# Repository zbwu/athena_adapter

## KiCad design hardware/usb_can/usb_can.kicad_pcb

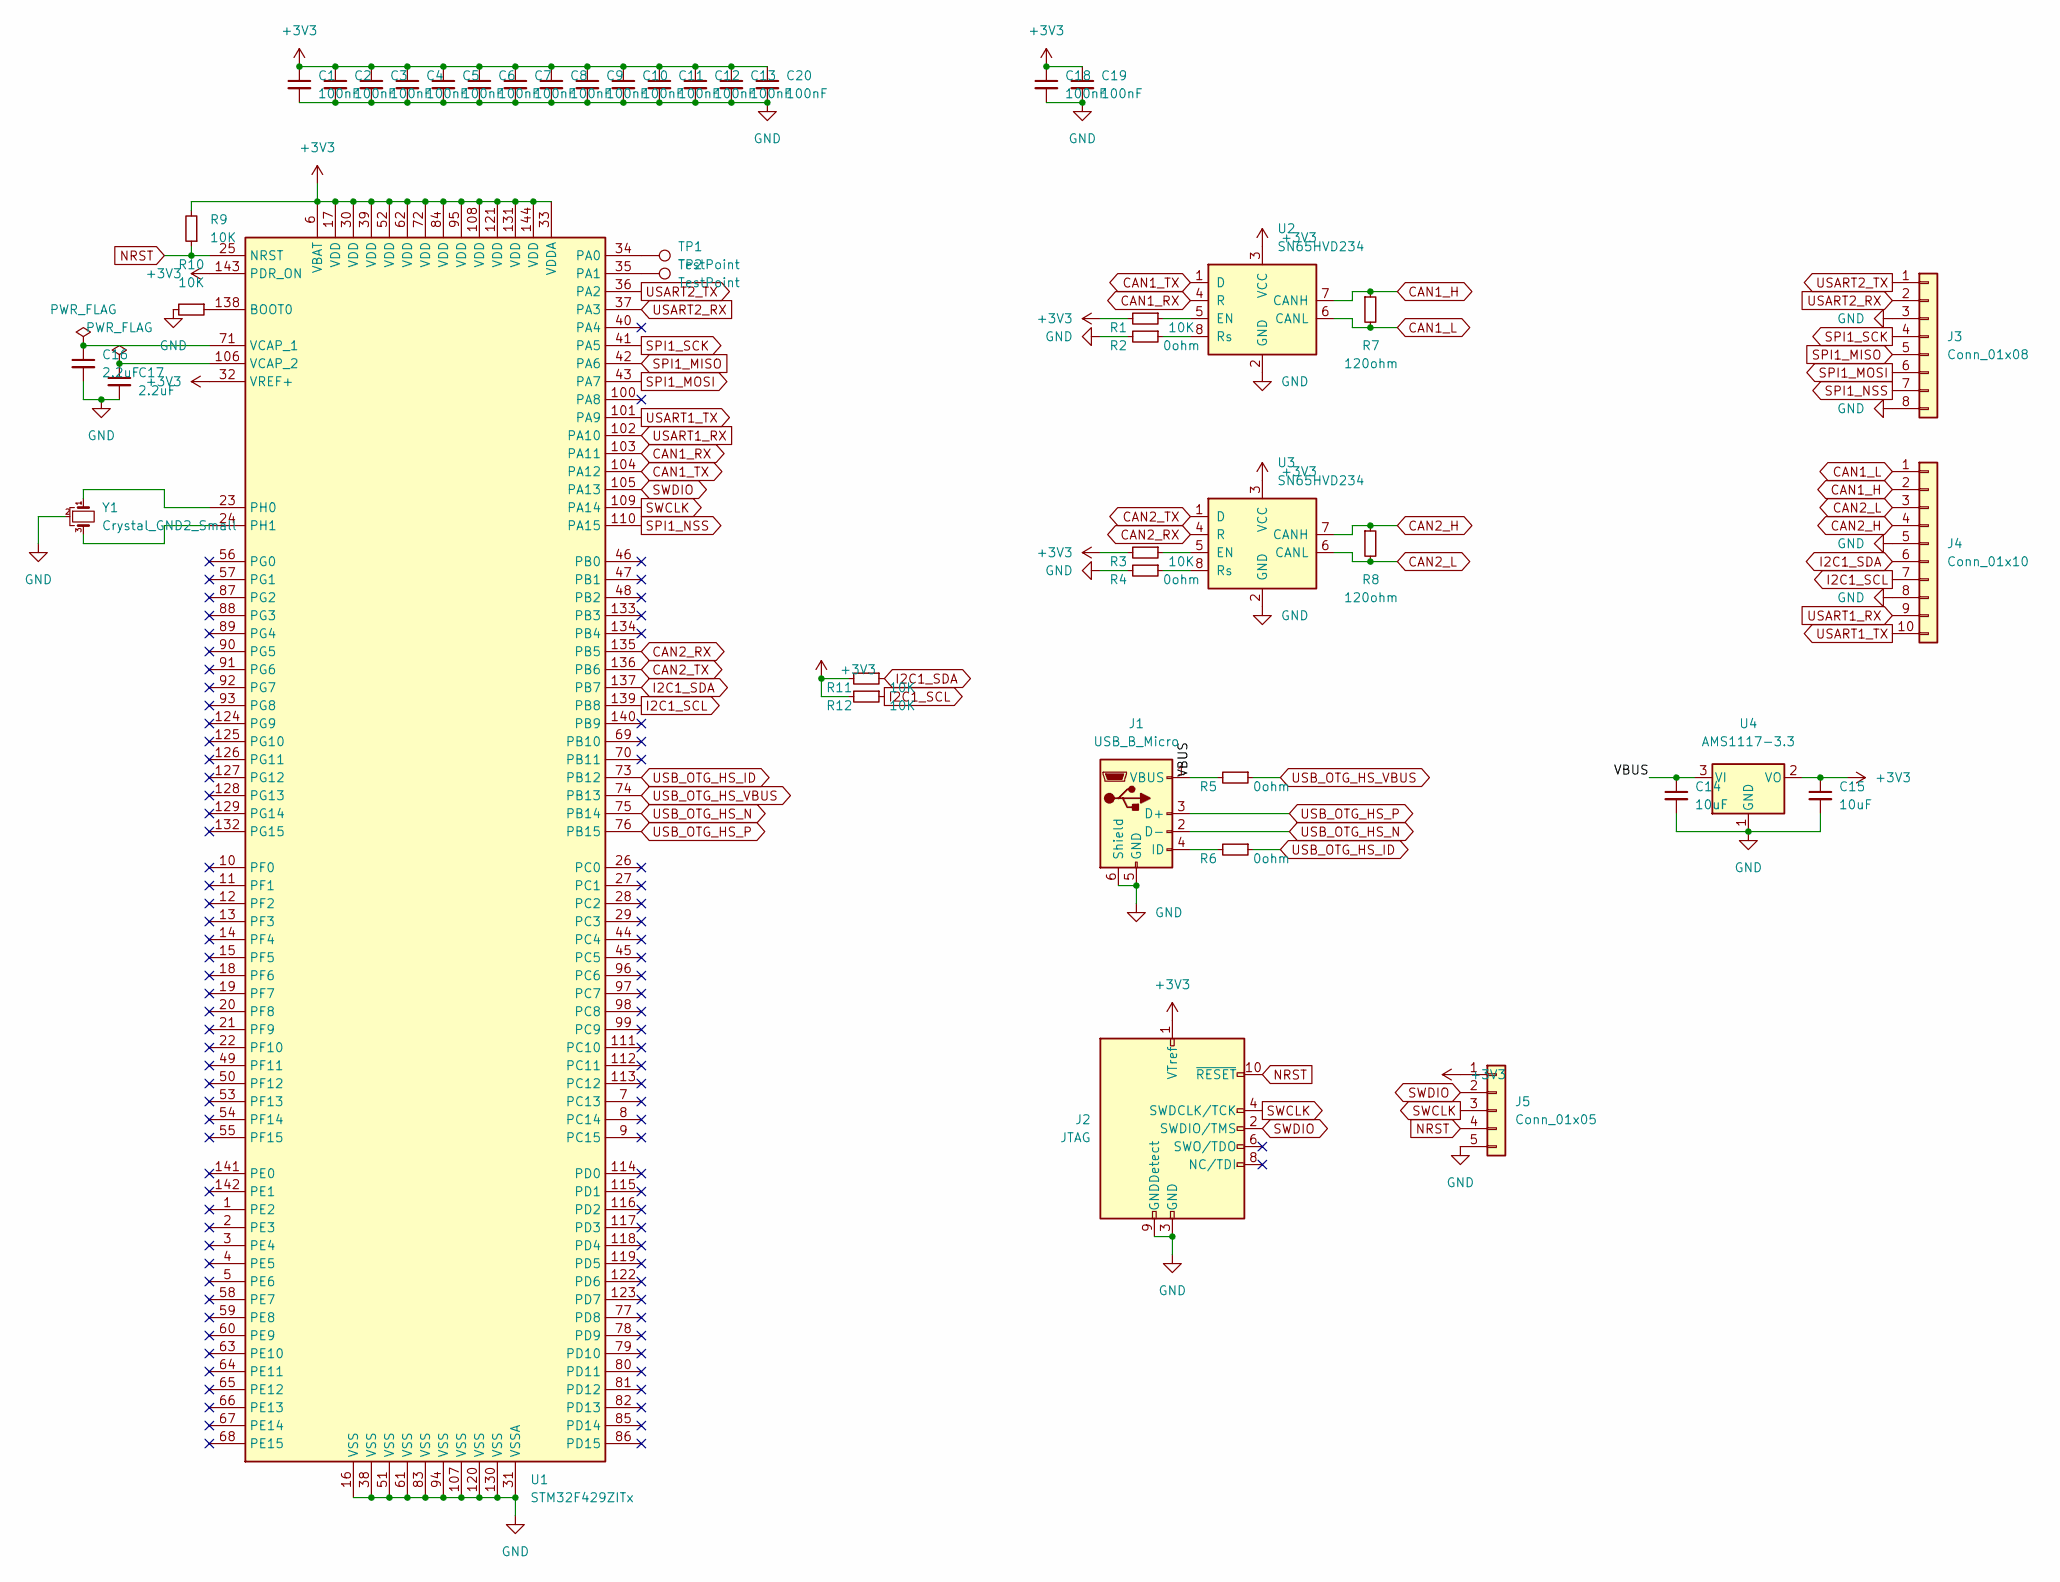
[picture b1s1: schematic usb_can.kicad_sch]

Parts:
C1, C2, C3, C4, C5, C6, C7, C8, C9, C10, C11, C12, C13, C18, C19, C20: 100nF; C_0603_1608Metric_Pad1.08x0.95mm_HandSolder
C14, C15: 10uF; C_1206_3216Metric_Pad1.33x1.80mm_HandSolder
C16, C17: 2.2uF; C_1206_3216Metric_Pad1.33x1.80mm_HandSolder
J1: USB_B_Micro; USB_Micro-B_YourCee_7.2_16Pin
J2: JTAG; PinHeader_2x05_P1.27mm_Vertical_SMD
J3: Conn_01x08; Harwin_M20-89008xx_1x08_P2.54mm_Horizontal
J4: Conn_01x10; Harwin_M20-89010xx_1x10_P2.54mm_Horizontal
J5: Conn_01x05; Harwin_M20-89005xx_1x05_P2.54mm_Horizontal
R1, R3, R9, R10, R11, R12: 10K; R_0603_1608Metric_Pad0.98x0.95mm_HandSolder
R2, R4, R5, R6: 0ohm; R_0603_1608Metric_Pad0.98x0.95mm_HandSolder
R7, R8: 120ohm; R_0603_1608Metric_Pad0.98x0.95mm_HandSolder
TP1, TP2: TestPoint; TestPoint_Pad_D1.5mm
U1: STM32F429ZITx; LQFP-144_20x20mm_P0.5mm
U2, U3: SN65HVD234; SOIC-8_3.9x4.9mm_P1.27mm
U4: AMS1117-3.3; SOT-223-3_TabPin2
Y1: Crystal_GND2_Small; CSTNE8M00GH5L000R0

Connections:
+3V3: C1.1, C2.1, C3.1, C4.1, C5.1, C6.1, C7.1, C8.1, C9.1, C10.1, C11.1, C12.1, C13.1, C15.1, C18.1, C19.1, C20.1, J2.1 (VTref), J5.1, R1.2, R3.2, R9.2, R11.2, R12.2, U1.6 (VBAT), U1.17 (VDD), U1.30 (VDD), U1.32 (VREF+), U1.33 (VDDA), U1.39 (VDD), U1.52 (VDD), U1.62 (VDD), U1.72 (VDD), U1.84 (VDD), U1.95 (VDD), U1.108 (VDD), U1.121 (VDD), U1.131 (VDD), U1.143 (PDR_ON), U1.144 (VDD), U2.3 (VCC), U3.3 (VCC), U4.2 (VO)
/VBUS: C14.1, J1.1 (VBUS), R5.2, U4.3 (VI)
CAN1_H: J4.2, R7.1, U2.7 (CANH)
CAN1_L: J4.1, R7.2, U2.6 (CANL)
CAN1_RX: U1.103 (PA11), U2.4 (R)
CAN1_TX: U1.104 (PA12), U2.1 (D)
CAN2_H: J4.4, R8.1, U3.7 (CANH)
CAN2_L: J4.3, R8.2, U3.6 (CANL)
CAN2_RX: U1.135 (PB5), U3.4 (R)
CAN2_TX: U1.136 (PB6), U3.1 (D)
GND: C1.2, C2.2, C3.2, C4.2, C5.2, C6.2, C7.2, C8.2, C9.2, C10.2, C11.2, C12.2, C13.2, C14.2, C15.2, C16.2, C17.2, C18.2, C19.2, C20.2, J1.5 (GND), J1.6 (Shield), J2.3 (GND), J2.5 (GND), J2.9 (GNDDetect), J3.3, J3.8, J4.5, J4.8, J5.5, R2.2, R4.2, R10.2, U1.16 (VSS), U1.31 (VSSA), U1.38 (VSS), U1.51 (VSS), U1.61 (VSS), U1.83 (VSS), U1.94 (VSS), U1.107 (VSS), U1.120 (VSS), U1.130 (VSS), U2.2 (GND), U3.2 (GND), U4.1 (GND), Y1.2
I2C1_SCL: J4.7, R12.1, U1.139 (PB8)
I2C1_SDA: J4.6, R11.1, U1.137 (PB7)
NRST: J2.10 (~RESET), J5.4, R9.1, U1.25 (NRST)
unnamed: C16.1, U1.71 (VCAP_1)
unnamed: C17.1, U1.106 (VCAP_2)
unnamed: J1.4 (ID), R6.2
unnamed: R1.1, U2.5 (EN)
unnamed: R2.1, U2.8 (Rs)
unnamed: R3.1, U3.5 (EN)
unnamed: R4.1, U3.8 (Rs)
unnamed: R10.1, U1.138 (BOOT0)
unnamed: TP1.1, U1.34 (PA0)
unnamed: TP2.1, U1.35 (PA1)
unnamed: U1.23 (PH0), Y1.1
unnamed: U1.24 (PH1), Y1.3
SPI1_MISO: J3.5, U1.42 (PA6)
SPI1_MOSI: J3.6, U1.43 (PA7)
SPI1_NSS: J3.7, U1.110 (PA15)
SPI1_SCK: J3.4, U1.41 (PA5)
SWCLK: J2.4 (SWDCLK/TCK), J5.3, U1.109 (PA14)
SWDIO: J2.2 (SWDIO/TMS), J5.2, U1.105 (PA13)
USART1_RX: J4.9, U1.102 (PA10)
USART1_TX: J4.10, U1.101 (PA9)
USART2_RX: J3.2, U1.37 (PA3)
USART2_TX: J3.1, U1.36 (PA2)
USB_OTG_HS_ID: R6.1, U1.73 (PB12)
USB_OTG_HS_N: J1.2 (D-), U1.75 (PB14)
USB_OTG_HS_P: J1.3 (D+), U1.76 (PB15)
USB_OTG_HS_VBUS: R5.1, U1.74 (PB13)

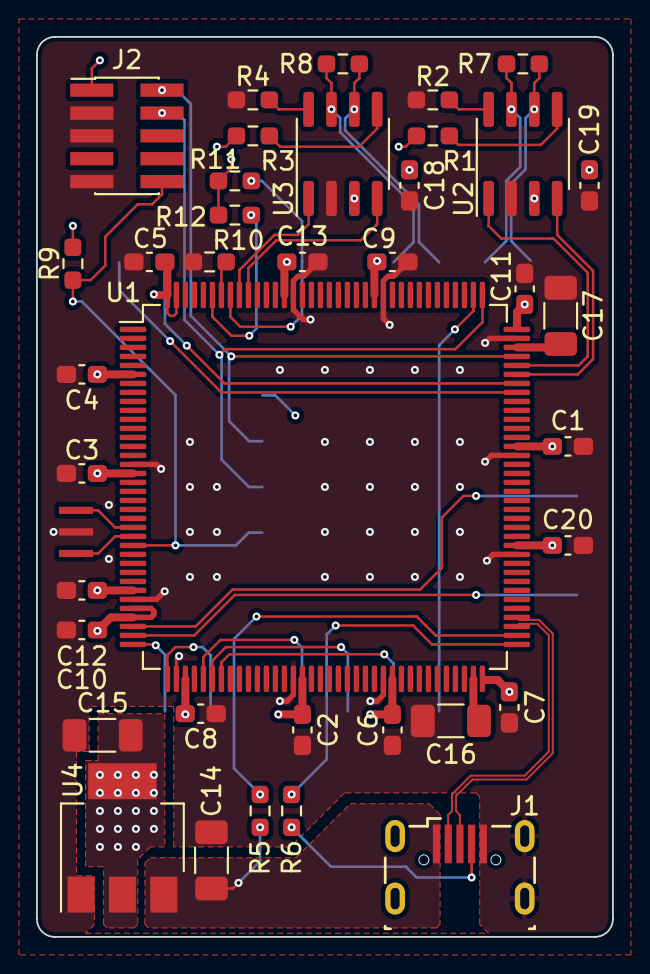
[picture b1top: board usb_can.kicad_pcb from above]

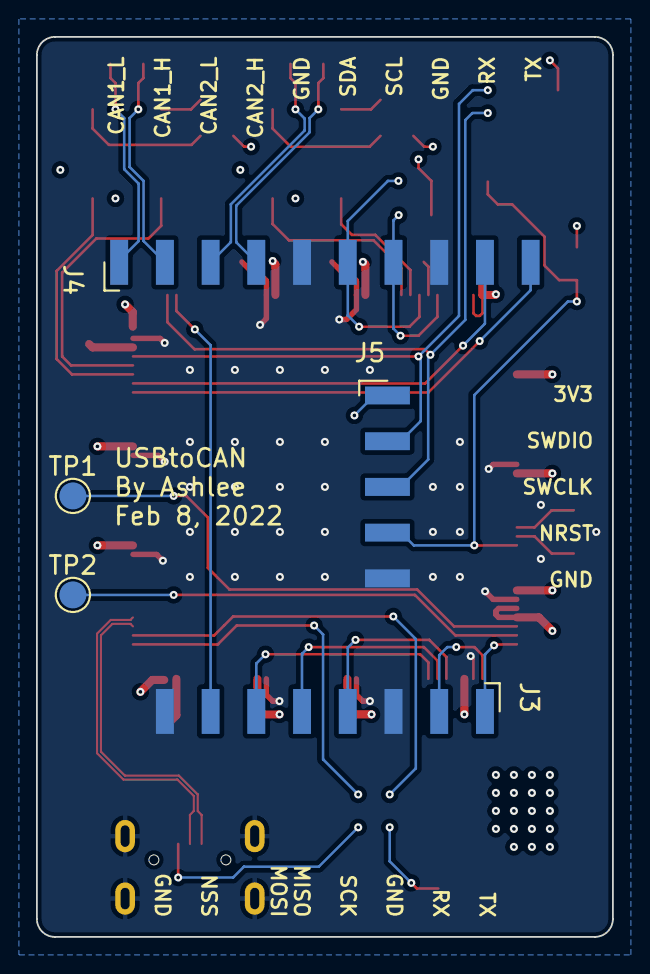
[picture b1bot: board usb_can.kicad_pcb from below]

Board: 4 copper layers, 32.0 x 50.0 mm, 44 parts (5 on the bottom side), 40 nets.

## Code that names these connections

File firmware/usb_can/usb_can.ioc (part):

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Mcu.Name=STM32F429ZITx
Mcu.Package=LQFP144
Mcu.UserName=STM32F429ZITx
PA11.Mode=CAN_Activate
PA11.Signal=CAN1_RX
PA12.Mode=CAN_Activate
PA12.Signal=CAN1_TX
PA13.Mode=Serial_Wire
PA13.Signal=SYS_JTMS-SWDIO
PA14.Mode=Serial_Wire
PA14.Signal=SYS_JTCK-SWCLK
PB14.Mode=Device_Only_FS
PB14.Signal=USB_OTG_HS_DM
PB15.Mode=Device_Only_FS
PB15.Signal=USB_OTG_HS_DP
PH0/OSC_IN.Mode=HSE-External-Oscillator
PH0/OSC_IN.Signal=RCC_OSC_IN
PH1/OSC_OUT.Mode=HSE-External-Oscillator
PH1/OSC_OUT.Signal=RCC_OSC_OUT
RCC.HSE_VALUE=8000000
RCC.SYSCLKFreq_VALUE=168000000
RCC.SYSCLKSource=RCC_SYSCLKSOURCE_PLLCLK
board=custom

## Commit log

2022-08-12 add MotorCtrl
2022-08-12 add base firmware, generate by stm32cubemx
2022-08-12 add usb-can protocol support
2022-08-12 add usb-can schematic and pcb layout
